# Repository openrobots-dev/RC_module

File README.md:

RC_module
=========

R2P RC module

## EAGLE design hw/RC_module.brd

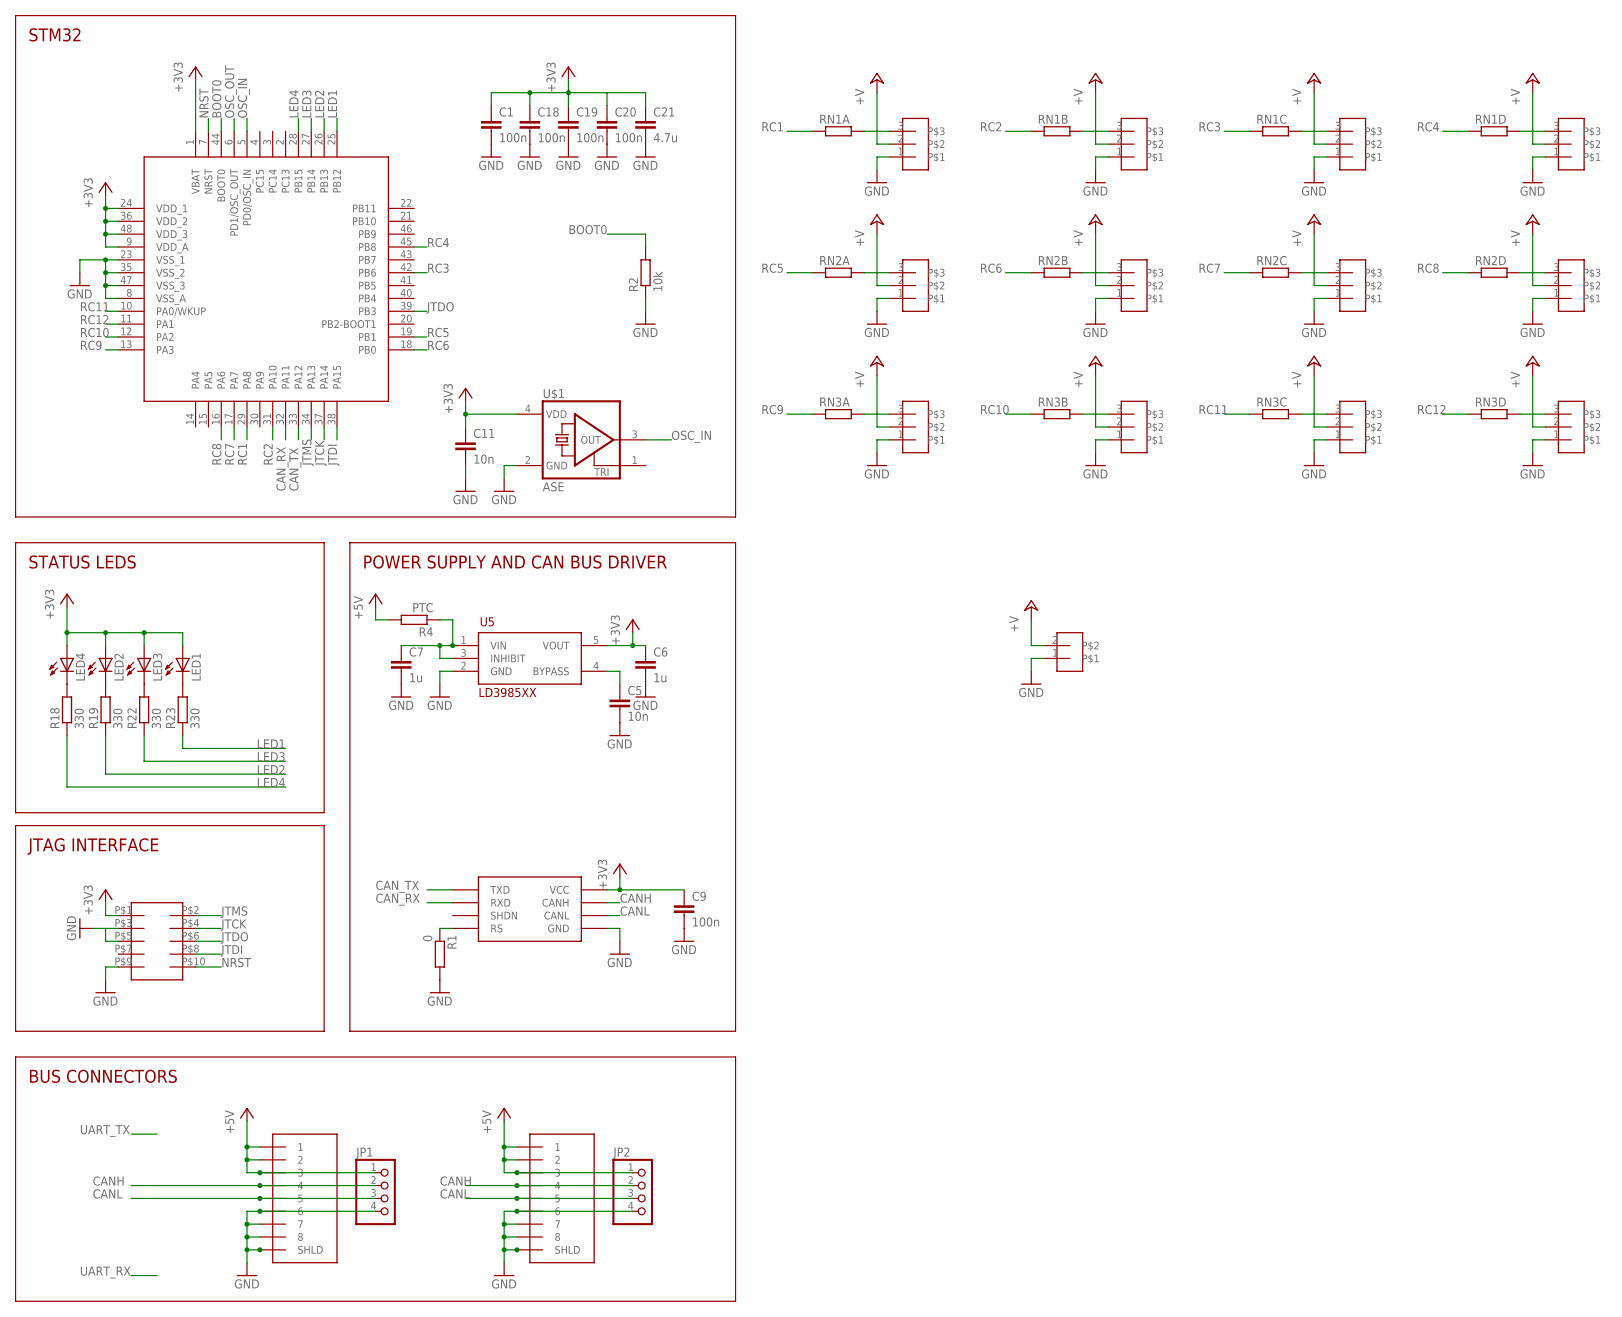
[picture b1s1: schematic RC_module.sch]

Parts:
1, 2: RJ45-43860; 0438600010
C1, C9, C18, C19, C20: 100n; C0603
C5, C11: 10n; C0603
C6, C7: 1u; C0603
C21: 4.7u; C0805
JP1, JP2: PINHD-1X4; 1X04
LED1, LED2, LED3, LED4: LEDCHIPLED_0805; CHIPLED_0805
R1: 0; R0603
R2: 10k; R0603
R4: PTC; R0603
R18, R19, R22, R23: 330; R0603
RN1, RN2, RN3: RESISTOR_ARRAY_4; RN8P-4R-CRA06S
SOT1: MAX3051; SOT23-8L
U1: STM32F103CX; LQFP48
U5: LD3985XX; SOT23-5L
U$1: ASE
U$2, U$3, U$5, U$6, U$7, U$8, U$9, U$10, U$11, U$12, U$13, U$14: PINHD-3; 1X03
U$4: FTSH-105
U$15: SCREWTERMINAL_3-3; SCREWTERMINAL-3.5MM-2

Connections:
+3V3: C1.1, C6.1, C9.1, C11.1, C18.1, C19.1, C20.1, C21.1, LED1.A, LED2.A, LED3.A, LED4.A, SOT1.P$3 (VCC), U1.1 (VBAT), U1.9 (VDD_A), U1.24 (VDD_1), U1.36 (VDD_2), U1.48 (VDD_3), U5.5 (VOUT), U$1.4 (VDD), U$4.P$1
+5V: 1.P$1 (1), 1.P$2 (2), 1.P$3 (3), 2.P$1 (1), 2.P$2 (2), 2.P$3 (3), JP1.1, JP2.1, R4.2
+V: U$2.2, U$3.2, U$5.2, U$6.2, U$7.2, U$8.2, U$9.2, U$10.2, U$11.2, U$12.2, U$13.2, U$14.2, U$15.2
BOOT0: R2.2, U1.44 (BOOT0)
CANH: 1.P$4 (4), 2.P$4 (4), JP1.2, JP2.2, SOT1.P$7 (CANH)
CANL: 1.P$5 (5), 2.P$5 (5), JP1.3, JP2.3, SOT1.P$6 (CANL)
CAN_RX: SOT1.P$4 (RXD), U1.32 (PA11)
CAN_TX: SOT1.P$1 (TXD), U1.33 (PA12)
GND: 1.P$6 (6), 1.P$7 (7), 1.P$8 (8), 1.P$9 (SHLD), 1.P$10, 2.P$6 (6), 2.P$7 (7), 2.P$8 (8), 2.P$9 (SHLD), 2.P$10, C1.2, C5.2, C6.2, C7.2, C9.2, C11.2, C18.2, C19.2, C20.2, C21.2, JP1.4, JP2.4, R1.2, R2.1, SOT1.P$2 (GND), U1.8 (VSS_A), U1.23 (VSS_1), U1.35 (VSS_2), U1.47 (VSS_3), U5.2 (GND), U$1.2 (GND), U$2.1, U$3.1, U$4.P$3, U$4.P$9, U$5.1, U$6.1, U$7.1, U$8.1, U$9.1, U$10.1, U$11.1, U$12.1, U$13.1, U$14.1, U$15.1
JTCK: U1.37 (PA14), U$4.P$4
JTDI: U1.38 (PA15), U$4.P$8
JTDO: U1.39 (PB3), U$4.P$6
JTMS: U1.34 (PA13), U$4.P$2
LED1: R23.1, U1.25 (PB12)
LED2: R19.1, U1.26 (PB13)
LED3: R22.1, U1.27 (PB14)
LED4: R18.1, U1.28 (PB15)
unnamed: R1.1, SOT1.P$8 (RS)
unnamed: RN1.8 (2), U$2.3
unnamed: C5.1, U5.4 (BYPASS)
unnamed: C7.1, R4.1, U5.1 (VIN), U5.3 (INHIBIT)
unnamed: RN1.7 (2), U$3.3
unnamed: RN1.6 (2), U$5.3
unnamed: RN1.5 (2), U$6.3
unnamed: RN2.8 (2), U$7.3
unnamed: RN2.7 (2), U$8.3
unnamed: RN2.6 (2), U$9.3
unnamed: RN2.5 (2), U$10.3
unnamed: RN3.8 (2), U$11.3
unnamed: RN3.7 (2), U$12.3
unnamed: LED4.C, R18.2
unnamed: RN3.6 (2), U$13.3
unnamed: RN3.5 (2), U$14.3
unnamed: LED2.C, R19.2
unnamed: LED3.C, R22.2
unnamed: LED1.C, R23.2
NRST: U1.7 (NRST), U$4.P$10
OSC_IN: U1.5 (PD0/OSC_IN), U$1.3 (OUT)
OSC_OUT: U1.6 (PD1/OSC_OUT)
RC1: RN1.1, U1.29 (PA8)
RC2: RN1.2 (1), U1.31 (PA10)
RC3: RN1.3 (1), U1.42 (PB6)
RC4: RN1.4 (1), U1.45 (PB8)
RC5: RN2.1, U1.19 (PB1)
RC6: RN2.2 (1), U1.18 (PB0)
RC7: RN2.3 (1), U1.17 (PA7)
RC8: RN2.4 (1), U1.16 (PA6)
RC9: RN3.1, U1.13 (PA3)
RC10: RN3.2 (1), U1.12 (PA2)
RC11: RN3.3 (1), U1.10 (PA0/WKUP)
RC12: RN3.4 (1), U1.11 (PA1)

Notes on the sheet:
STM32
POWER SUPPLY AND CAN BUS DRIVER
STATUS LEDS
JTAG INTERFACE
BUS CONNECTORS

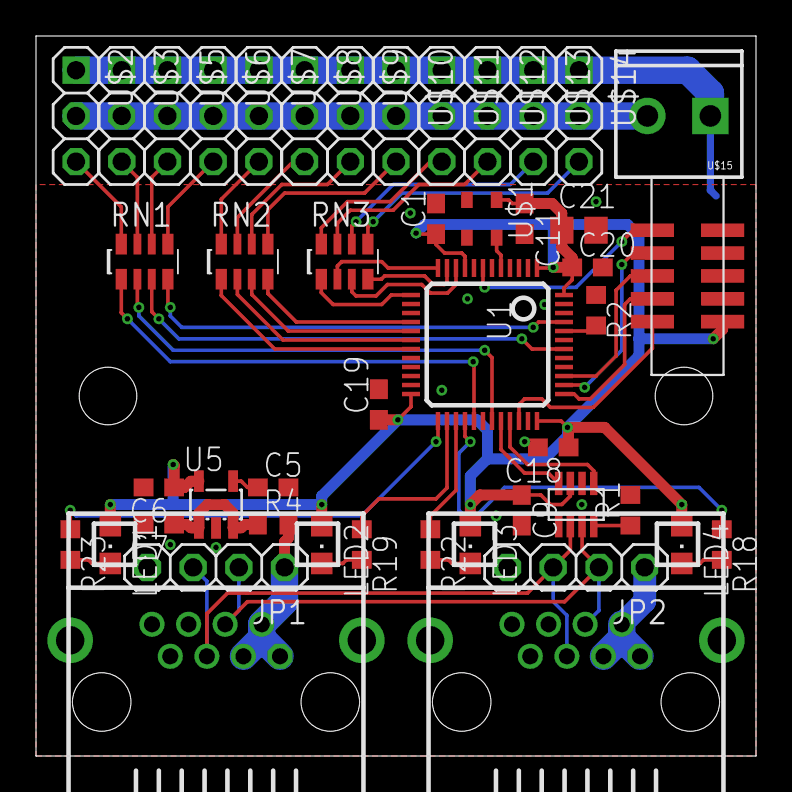
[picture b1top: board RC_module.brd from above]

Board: 2 copper layers, 40.0 x 40.0 mm, 46 parts (0 on the bottom side), 50 nets.

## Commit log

2013-10-24 layout completed
